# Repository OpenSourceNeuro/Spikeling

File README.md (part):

<div align="center">

# **Spikeling v3**

### **An open-source hardware + software platform for neuroscience teaching and outreach:**  

A hands-on “artificial spiking neuron” running the **Izhikevich model** on an **ESP32**, with a desktop **GUI** for visualization, interaction, and data export.

<p>

</p>

<p align="right">
  developed by M.J.Y. Zimmermann<br>
  maintained by P. Rignanese & A. Koumoundourou<br>
  based on an original idea by T. Baden
</p>

</div>

This project is licensed under the [GNU General Public License v3.0](https://www.gnu.org/licenses/gpl-3.0.en.html)
<br>
The hardware is licensed under the [ CERN-OHL-S-2.0](https://gitlab.com/ohwr/project/cernohl/-/wikis/uploads/b88fd806c337866bff655f2506f23d37/cern_ohl_s_v2_user_guide.txt)

## Contents

- [What is Spikeling?](#what-is-spikeling)
- [Spikeling in academia & outreach](#spikeling-in-academia--outreach)
- [A brief summary of Spikeling functions](#a-brief-summary-of-spikeling-functions)
  - [Neurophysiology](#neurophysiology)
  - [Data analysis](#data-analysis)
  - [Neuron generator](#neuron-generator)
  - [Stimulus generator](#stimulus-generator)
  - [Multi-recording & networking](#multi-recording--networking-multi-unit-experiments)
  - [Fluorescence imaging simulation](#fluorescence-imaging-simulation)
  - [Exercises](#exercises)
- [Documentation](#documentation)
- [Contributing](#contributing)
- [License](#license)

---

<br>

<div align="center">

## What is Spikeling?

<br>

<p style='text-align: justify;'>
  Spikeling is an open-source neuroscience education platform designed to make core neurophysiology concepts teachable through hands-on experimentation, even in settings where traditional wet-lab electrophysiology is impractical.
</p>

<p style='text-align: justify;'>
  In many degree programs, students learn about action potentials and synaptic signalling largely through lectures or static datasets because living preparations, microscopes, amplifiers, and specialist supervision do not scale well to large cohorts. Spikeling addresses this gap with a low-cost “in silico neuron” implemented in hardware.
</p>

<p style='text-align: justify;'>
  The device runs the computationally efficient and versatile <strong>Izhikevich spiking neuron model</strong> in real time on an ESP32-based microcontroller, providing electrophysiology-style interaction: controlled stimulation, measurable membrane-voltage dynamics, spike output, and parameter manipulation to explore firing regimes, adaptation, and input integration.
</p>

<p style='text-align: justify;'>
  A dedicated <strong>cross-platform desktop GUI</strong> supports real-time plotting, experiment control, and recording/export to standard formats—enabling teaching modules that extend beyond neurophysiology into protocol design, data collection, analysis pipelines, and model-based reasoning.
</p>

</div>

<br>

<div align="center">

<h6 align="center">Two spikeling units (red and green), that are synchronously stimulated (white cables), synapse with a third unit (blue).</h6>

</div>

---

<br>

<div align="center">

## Spikeling in academia & outreach

<br>

<p style='text-align: justify;'>
  The spikeling project emerged from local needs to teach neuroscience class modules for direct interaction with <strong>neuron physiology, data analysis, fluorescence imaging, protocol design, etc.</strong>
</p>

<p style='text-align: justify;'>
  The aim was to provide <strong>hands-on experience</strong> on how neurons encode information and how diverse variables modulates their activities, while engaging students with <strong>crucial aspects of data collection, experimental limitations, methodology and statistical analysis.</strong>
</p>

<p style='text-align: justify;'>
  Spikeling is currently used in <strong>university teaching, computational neuroscience training, and outreach events</strong>. It is intentionally <strong>open (hardware + firmware + software)</strong> so educators can customize activities for their courses and contribute back to a shared pool of teaching material.
</p>

<table>
  <tr>
    <td width="33%">
      <br>
      <sub><b>Outreach demonstration of neuron activities to primary school student in Ghana (2025)</b></sub>
    </td>
    <td width="33%">
      <br>
      <sub><b>Hands-on electrophysiology-style experiments in Zambia (2025)</b></sub>
    </td>
    <td width="33%">
      <br>
      <sub><b>Small-group protocol design & parameter exploration in Rwanda (2024)</b></sub>
    </td>
  </tr>

</table>

</div>

***

<br>

<div align="center">

## A brief summary of Spikeling functions

<br>

<h3 align="left"> Neurophysiology:</h3></p>

<p style='text-align: justify;'>
  Spikeling implements the <strong>Izhikevich model</strong>, which “reproduces spiking and bursting behaviour of known type of cortical neurons. The model combines the <strong>biologically plausibility of Hodgkin-Huxley-type dynamics</strong> and the <strong>computational efficiency of integrate-and-fire neurons</strong>” <a href="https://ieeexplore.ieee.org/document/1257420"> E. M. Izhikevich, "Simple model of spiking neurons, 2003"</a>.
  This makes it well-suited for teaching as learners can move quickly between <strong>hypothesis → stimulation → observation → interpretation</strong>.
</p>

<p style='text-align: justify;'>
  Neurophysiology concepts are taught through electrophysiology-style interaction: students apply controlled inputs and directly observe membrane-voltage dynamics,
  thresholding, spike generation, and adaptation. This supports practical teaching objectives such as protocol design, parameter sensitivity, and reproducible experimentation.
</p>

<ul align="left">
  <li>
    <b>Patch-clamp style stimulation (current injection):</b>
    A simulated patch-clamp interface allows students to inject controlled current steps and waveforms.
    Learners can vary <b>amplitude</b>, <b>duration</b>, and <b>timing</b> to explore excitability, threshold, refractory effects, and spike-frequency adaptation.
  </li>

  <li>
    <b>Photo-sensitive input (photodiode / “photoreceptor”):</b>
    Spikeling includes a photodiode input that mimics sensory-driven current input.
    Students can test simple stimuli (e.g., flashlight pulses) and progress to controlled protocols using an external LED driven via the stimulus port
    (frequency/intensity). Advanced discussions can include response dynamics such as effective decay/recovery behaviour under repeated stimulation.
  </li>

  <li>
    <b>Synapses and networks (dendrites + axon):</b>
    Each unit provides <b>two dendritic inputs</b> with gain and polarity control (supporting excitatory and inhibitory effects) and <b>one axonal spike output</b>.
    This enables multi-unit experiments on coincidence detection, inhibition-driven gating, synchrony, and simple network motifs.
    Auxiliary units can be stimulated synchronously to keep network experiments controlled and reproducible.
  </li>
</ul>

<p style='text-align: justify;'>
  Together, these features let students reproduce classic teaching experiments:
  step-current response curves, threshold measurements, adaptation quantification, sensory-driven spiking, and basic synaptic/network computations—using the same device and workflow.
</p>

<br>

<h6 align="center">Left: Drawing on the acrylic cover of the Spikeling version 2.2, representing the controls knobs along with the input/ouput jacks.

Right: Spikeling GUI displaying the unit membrane voltage (red trace) while being light-stimulated by a controlled LED (blue trace) which generates input current (green trace).
</h6>

</div>

***

<div align="center">

<h3 align="left"> Data analysis</h3></p>

<p style='text-align: justify;'>
  Spikeling is designed to extend practical teaching beyond “watching spikes” into the full experimental workflow:
  <strong>recording</strong>, <strong>quality control</strong>, <strong>basic quantification</strong>, and <strong>export for reproducible analysis</strong>.
  This is particularly valuable in neuroscience curricula where students may have limited exposure to programming and data pipelines, yet are expected to interpret real experimental data.
</p>

<p style='text-align: justify;'>
Any data generated by Spikeling can be <strong>saved and exported</strong> for downstream analysis. The GUI also provides a lightweight,
<strong>built-in analysis</strong> layer that helps students validate recordings and immediately compute core measures such as spike detection and trial-averaged responses.
This supports in-class demonstrations, rapid iteration during labs, and structured home assignments.
</p>

<p style='text-align: justify;'>
  For advanced data analysis and basic statistics, <strong>python notebooks</strong> are provided to serve as template for the teaching staff. We are engage with the Spikeling community where users could share courses, exercises and data analysis scripts to be widely used in neuroscience and coding courses.
</p>

<ul align="left">
  <li>
    <b>Recording & export:</b>
    save time series (e.g., Vm, stimulus, derived currents, triggers) and export to standard formats (e.g., <b>CSV</b>) compatible with Python, MATLAB, R, Excel, etc.
  </li>
  <li>
    <b>Basic QC and annotation:</b>
    quickly verify signal integrity, confirm stimulus timing, and identify artefacts before committing to a full analysis workflow.
  </li>
  <li>
    <b>Spike detection and raster plots:</b>
    detect spikes from membrane-voltage traces and visualize them as rasters to introduce spike trains, variability, and stimulus-locked responses.
  </li>
  <li>
    <b>Trial alignment, looping, and averaging:</b>
    repeat identical stimulus protocols, align trials, and compute averaged traces and spike-rate summaries—making it easy to teach concepts like reliability,
    response variability, and signal-to-noise.
  </li>
  <li>
    <b>Bridge to coding modules:</b>
    provide exported datasets and template <b>Python notebooks</b> so teaching staff can scaffold progressively from GUI-based inspection to student-written analysis code.
  </li>
</ul>

<p style='text-align: justify;'>
  In short, Spikeling supports a gradual learning curve: students can begin with GUI-based inspection and built-in metrics,
  then transition to reproducible, script-based analysis using the exact same datasets—mirroring modern research practice.
</p>
<br>

<h6 align="center">Left: Displayed data from the previous experiment (light stimulation) spikes are detected and ploted along the Vm trace (red). Right: Traces looped and averaged showing the spike rate (white), the raster plot (red dots), the averaged Vm recording (red) and the averaged input current (green)</h6>

</div>

***

<div align="center">

<h3 align="left"> Neuron generator</h3></p>

<p style='text-align: justify;'>
  The <strong>Neuron Generator</strong> is an interactive space for exploring the Izhikevich model beyond “playing with a few knobs”.
  It is designed to help students connect <strong>model parameters</strong> to <strong>observable firing behaviours</strong> (e.g., tonic spiking, bursting, adaptation, rebound, irregular firing),
  and to build intuition for how different neurons can emerge from the same compact set of equations.
</p>

<p style='text-align: justify;'>
  In practice, the Neuron Generator lets learners rapidly prototype neuron “types” by adjusting Izhikevich parameters and immediately observing
  how the neuron responds to standardized stimuli. This encourages a scientific workflow: formulate a hypothesis (e.g., “increasing adaptation should reduce firing rate over time”),
  test it with controlled stimulation, then iterate.
</p>

<ul align="left">
  <li><b>Explore firing regimes:</b> interactively vary Izhikevich parameters and observe changes in excitability, thresholding, bursting, and adaptation.</li>
  <li><b>Compare neurons under identical protocols:</b> run the same stimulus recipe on multiple parameter sets to build mechanistic intuition.</li>
  <li><b>Create & share presets:</b> save custom neuron parameter sets for labs, assignments, or reproducible classroom demonstrations.</li>
  <li><b>Bridge theory and experiment:</b> connect equations/parameters to patch-clamp-style readouts (Vm traces, spike trains, firing-rate changes).</li>
</ul>

<br>

<h6 align="center">GUI displaying the “Neuron Generator” page where users can appreciate the model underlying Spikeling activity and from which they can generate unique neuron to further run on Spikeling.</h6>

</div>

***

<div align="center">

<h3 align="left">Stimulus generator:</h3>

<p style='text-align: justify;'>
  Spikeling includes a dedicated <strong>Stimulus Generator</strong> to teach one of the most important (and often under-taught) parts of experimental neuroscience:
  <strong>protocol design</strong>. While Spikeling board only has a simple repeated square-wave stimulus (useful for classic current-step experiments and LED/light stimulation),
  the Stimulus Generator encourages students to move beyond “turning knobs” and instead design inputs that directly test experimental hypotheses.
</p>

<p style='text-align: justify;'>
  Users can create and iterate custom stimuli—such as <strong>step families</strong>, <strong>sinusoids</strong>, <strong>chirps</strong>, <strong>pulse trains</strong>, and <strong>binary/noise-like</strong> sequences—
  then apply them to current injection or light stimulation. A built-in <strong>stimulus preview</strong> allows learners to verify waveform timing, amplitude, and repetition structure
  <em>before</em> running an experiment, reinforcing good practice around sanity checks and reproducibility.
</p>

<ul align="left">
  <li><b>From standard to custom protocols:</b> start with square pulses and progress to structured waveforms used in electrophysiology and systems neuroscience.</li>
  <li><b>Preview before running:</b> confirm duration, inter-stimulus intervals, amplitude scaling, and repetition count to avoid protocol errors.</li>
  <li><b>Reproducible experimentation:</b> define explicit parameters to enable trial averaging and fair comparisons across neuron modes or conditions.</li>
  <li><b>Hypothesis-driven design:</b> link stimulus structure to questions like threshold, adaptation time constants, resonance, and response reliability under noise.</li>
</ul>

<br>

  <h6 align="center">
    Stimulus Generator examples (with preview). Left: classic electrophysiology-style step family (10 steps, 10 a.u. increment, 25 ms per step, 5 ms rest at 0 a.u.).
    Right: sine-wave stimulus (50 a.u. amplitude, 20 Hz, 250 ms duration, 100 ms rest at 0 a.u.).
  </h6>

</div>

***

<div align="center">

<h3 align="left">Multi-recording & networking (multi-unit experiments):</h3>

<p style='text-align: justify;'>
  A key strength of Spikeling is that it can be scaled from a single “neuron” demo to <strong>small, interpretable networks</strong>.
  Each unit provides an <strong>axonal spike output</strong> and two <strong>dendritic (synaptic) inputs</strong>, enabling multiple Spikelings to be physically connected
  and studied as a functional circuit. This makes it possible to teach network-level computation using the same workflow as single-cell experiments:
  controlled stimulation, direct observation, and quantitative comparison.
</p>

<p style='text-align: justify;'>
  Importantly, each synaptic input can be configured as <strong>excitatory or inhibitory</strong> (via the synaptic gain control), allowing learners to explore
  how the <strong>sign</strong> and <strong>strength</strong> of coupling shapes membrane dynamics and spiking output. The GUI supports <strong>multi-recording</strong> by plotting and saving,
  in the same session, the activity of the main unit alongside the incoming synaptic streams (and, when available, the associated presynaptic signals),
  which is essential for teaching causality, timing, and interaction effects.
</p>

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
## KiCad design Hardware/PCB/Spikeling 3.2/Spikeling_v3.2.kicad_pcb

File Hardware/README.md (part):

<div align="center">

# **Hardware design, assembly, and revision notes**

<p>

</p>

</div>

This folder contains the hardware side of **Spikeling**: board revisions, build notes, connector conventions, and practical guidance for bringing a unit from PCB to a working neuroscience teaching device.

Spikeling is an open hardware + software platform for hands-on neuroscience teaching and outreach. It exposes a spiking neuron model through real controls, real I/O, and real-time visualisation, allowing students to run electrophysiology-style experiments without a full wet-lab rig.

**Quick links**
- [Main repository](../)
- [Firmware folder](../Firmware)
- [Software folder](../Software)
- [Documentation folder](../Documentation)
- [Hardware documentation](https://opensourceneuro.github.io/Spikeling/hardware/)
- [Quickstart: hardware setup](https://opensourceneuro.github.io/Spikeling/quickstart/hardware-setup/)
- [Reference: pinout and connectors](https://opensourceneuro.github.io/Spikeling/reference/pinout-and-connectors/)
- [Reference: specs](https://opensourceneuro.github.io/Spikeling/reference/specs/)

<p align="right">
  developed by M.J.Y. Zimmermann<br>
  maintained by P. Rignanese & A. Koumoundourou<br>
  based on an original idea by T. Baden
</p>

---

## **1. What this folder is for**

Use the `Hardware` folder as the entry point for:

- PCB design files and revision history
- manufacturing outputs and sourcing material
- assembly notes and bring-up checks
- connector / wiring conventions
- calibration and troubleshooting notes
- hardware differences between Spikeling generations

This README is meant to help contributors, builders, and teaching staff quickly understand which board they have, how it differs from other revisions, and where to find the next level of detail.

---

## **2. Hardware families**

Spikeling currently exists in two official board families.

### **Spikeling v2.x**
- **Microcontroller:** ESP32 WROOM-32
- **USB connector:** mini-USB
- **USB behaviour:** USB-to-UART bridge (**CP210x**)
- **Driver requirement:** often required, especially on Windows
- **Neuron mode selection:** on-board **Mode** button
- **Preset neuron modes:** 12

### **Spikeling v3.x**
- **Microcontroller:** ESP32-S3 WROOM-1
- **USB connector:** USB-C
- **USB behaviour:** native USB (**USB CDC serial**)
- **Driver requirement:** typically no separate USB-UART driver required
- **Neuron mode selection:** from the **GUI**
- **Preset neuron modes:** 20
- **Additional hardware compared to v2.x:** external DAC IC
- **Additional convenience features:** LiPo power-control hardware and a dedicated control to disable the Vm LED

> In practice, both families support the same teaching workflow: stimulate the model neuron, observe Vm and spikes, connect units together, and record/export data. The main differences affect USB connection, firmware target, mode selection, and a few hardware conveniences.

---

## **3. Version 2 vs version 3 — practical differences**

### **Connection and setup**
- **v2.x** uses a CP210x USB-to-UART bridge, so serial detection depends on that driver being installed.
- **v3.x** uses the ESP32-S3 native USB interface and usually enumerates directly as a USB serial device.

### **User interaction**
- **v2.x** changes neuron behaviour using an on-board **Mode** button.
- **v3.x** moves neuron mode selection into the GUI, which makes classroom switching and software-driven workflows more convenient.

### **Analogue output hardware**
- **v3.x** adds an external DAC compared with **v2.x**, improving the hardware architecture for the newer board generation.

### **Power and convenience controls**
- **v3.x** adds hardware support for the LiPo extension and includes a control to disable the Vm LED.
- **v2.x** is the simpler earlier platform and is closer to the minimal USB-to-ESP32 teaching-board architecture.

### **How to identify them quickly**
- **mini-USB = v2.x**
- **USB-C = v3.x**

---

## **4. What Spikeling hardware does**

At the hardware level, Spikeling behaves like a compact teaching-oriented electrophysiology preparation:

- multiple input pathways contribute to the neuron’s total drive
- the board exposes a measurable membrane potential (**Vm**)
- threshold crossings generate discrete spike events
- the board streams signals to the desktop GUI for visualisation, stimulation, and recording

### **Main input pathways**
- current injection control
- on-board square-wave stimulus generator
- GUI-driven stimulus generator
- photodiode input for light stimulation
- Synapse 1 / Synapse 2 inputs from other Spikeling units

### **Main outputs**
- analogue **Vm**
- digital spike events
- stimulus output for external use
- real-time USB serial stream to the GUI

---

## **5. Controls and I/O philosophy**

Spikeling uses **3.5 mm stereo TRS jacks** to carry both analogue and digital signals with a shared ground.

### **TRS convention**
- **Tip (T)** = digital / TTL
- **Ring (R)** = analogue signal
- **Sleeve (S)** = ground

This makes the hardware compact and classroom-friendly: one cable can carry both a continuously varying signal and an event marker.

### **Typical signal roles**
- **Synaptic / axon output:** analogue = presynaptic Vm, digital = spike events
- **Stimulus output:** analogue = stimulus waveform, digital = PWM / timing signal
- **Synapse input 1 / 2:** receives a TRS feed from another unit
- **Current input:** receives an injected analogue waveform
- **Photodiode workflow:** an LED driven through the stimulus path can act as a controlled light stimulus

### **Common wiring patterns**
- **Axon output (unit A) → Synapse input (unit B)** for two-unit network experiments
- **Stimulus output → LED cable → photodiode** for controlled light stimulation
- **Stimulus output → current input** for waveform-based injected current experiments

> Ground continuity matters. Many noisy or unstable measurements are caused by missing or inconsistent ground reference on the TRS sleeve.

---

## **6. Core teaching-facing controls**

The exact silkscreen may vary slightly between revisions, but the core controls remain conceptually stable.

- **Current injection**: direct depolarising / hyperpolarising drive
- **Stimulus strength**: amplitude of the on-board square-wave drive
- **Stimulus frequency**: repetition rate of the on-board stimulus
- **Noise**: Gaussian noise added to the input drive
- **Photo gain (±)**: gain and polarity of the photodiode input
- **Synapse 1 gain (±)**: excitatory or inhibitory strength of synapse 1
- **Synapse 2 gain (±)**: excitatory or inhibitory strength of synapse 2
- **Reset**: return the board to a known state
- **Buzzer mute**: disable spike audio feedback

### **Revision-specific controls**
- **v2.x:** Mode button selects one of 12 preset Izhikevich parameter sets
- **v3.x:** neuron mode is selected in the GUI, and the board adds:
  - **Vm LED disable**
  - **LiPo power switch / power-control hardware**

---

## **7. Minimum hardware needed to use a board**

### **For either generation**
- one Spikeling unit
- one data-capable USB cable
- at least one **3.5 mm TRS stereo cable**
- a computer running the GUI
- optionally, an LED stimulus cable for photodiode experiments

### **Board-specific USB cables**
- **v2.x:** mini-USB data cable
- **v3.x:** USB-C data cable

### **Recommended extras**
- powered USB hub
- spare TRS patch cables
- TRS-to-breakout adapter(s)
- multimeter
- optional oscilloscope or logic analyser for debugging

---

## **8. Quick bring-up checklist**

Before troubleshooting firmware or GUI issues, confirm the physical layer first.

- I know whether the board is **v2.x** or **v3.x**
- I am using a **data-capable** USB cable
- The board appears as a serial device on the computer
- For **v2.x**, the **CP210x** driver is installed
- I have at least one known-good **TRS** cable
- I understand the **Tip / Ring / Sleeve** mapping
- No other application is already holding the serial port
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
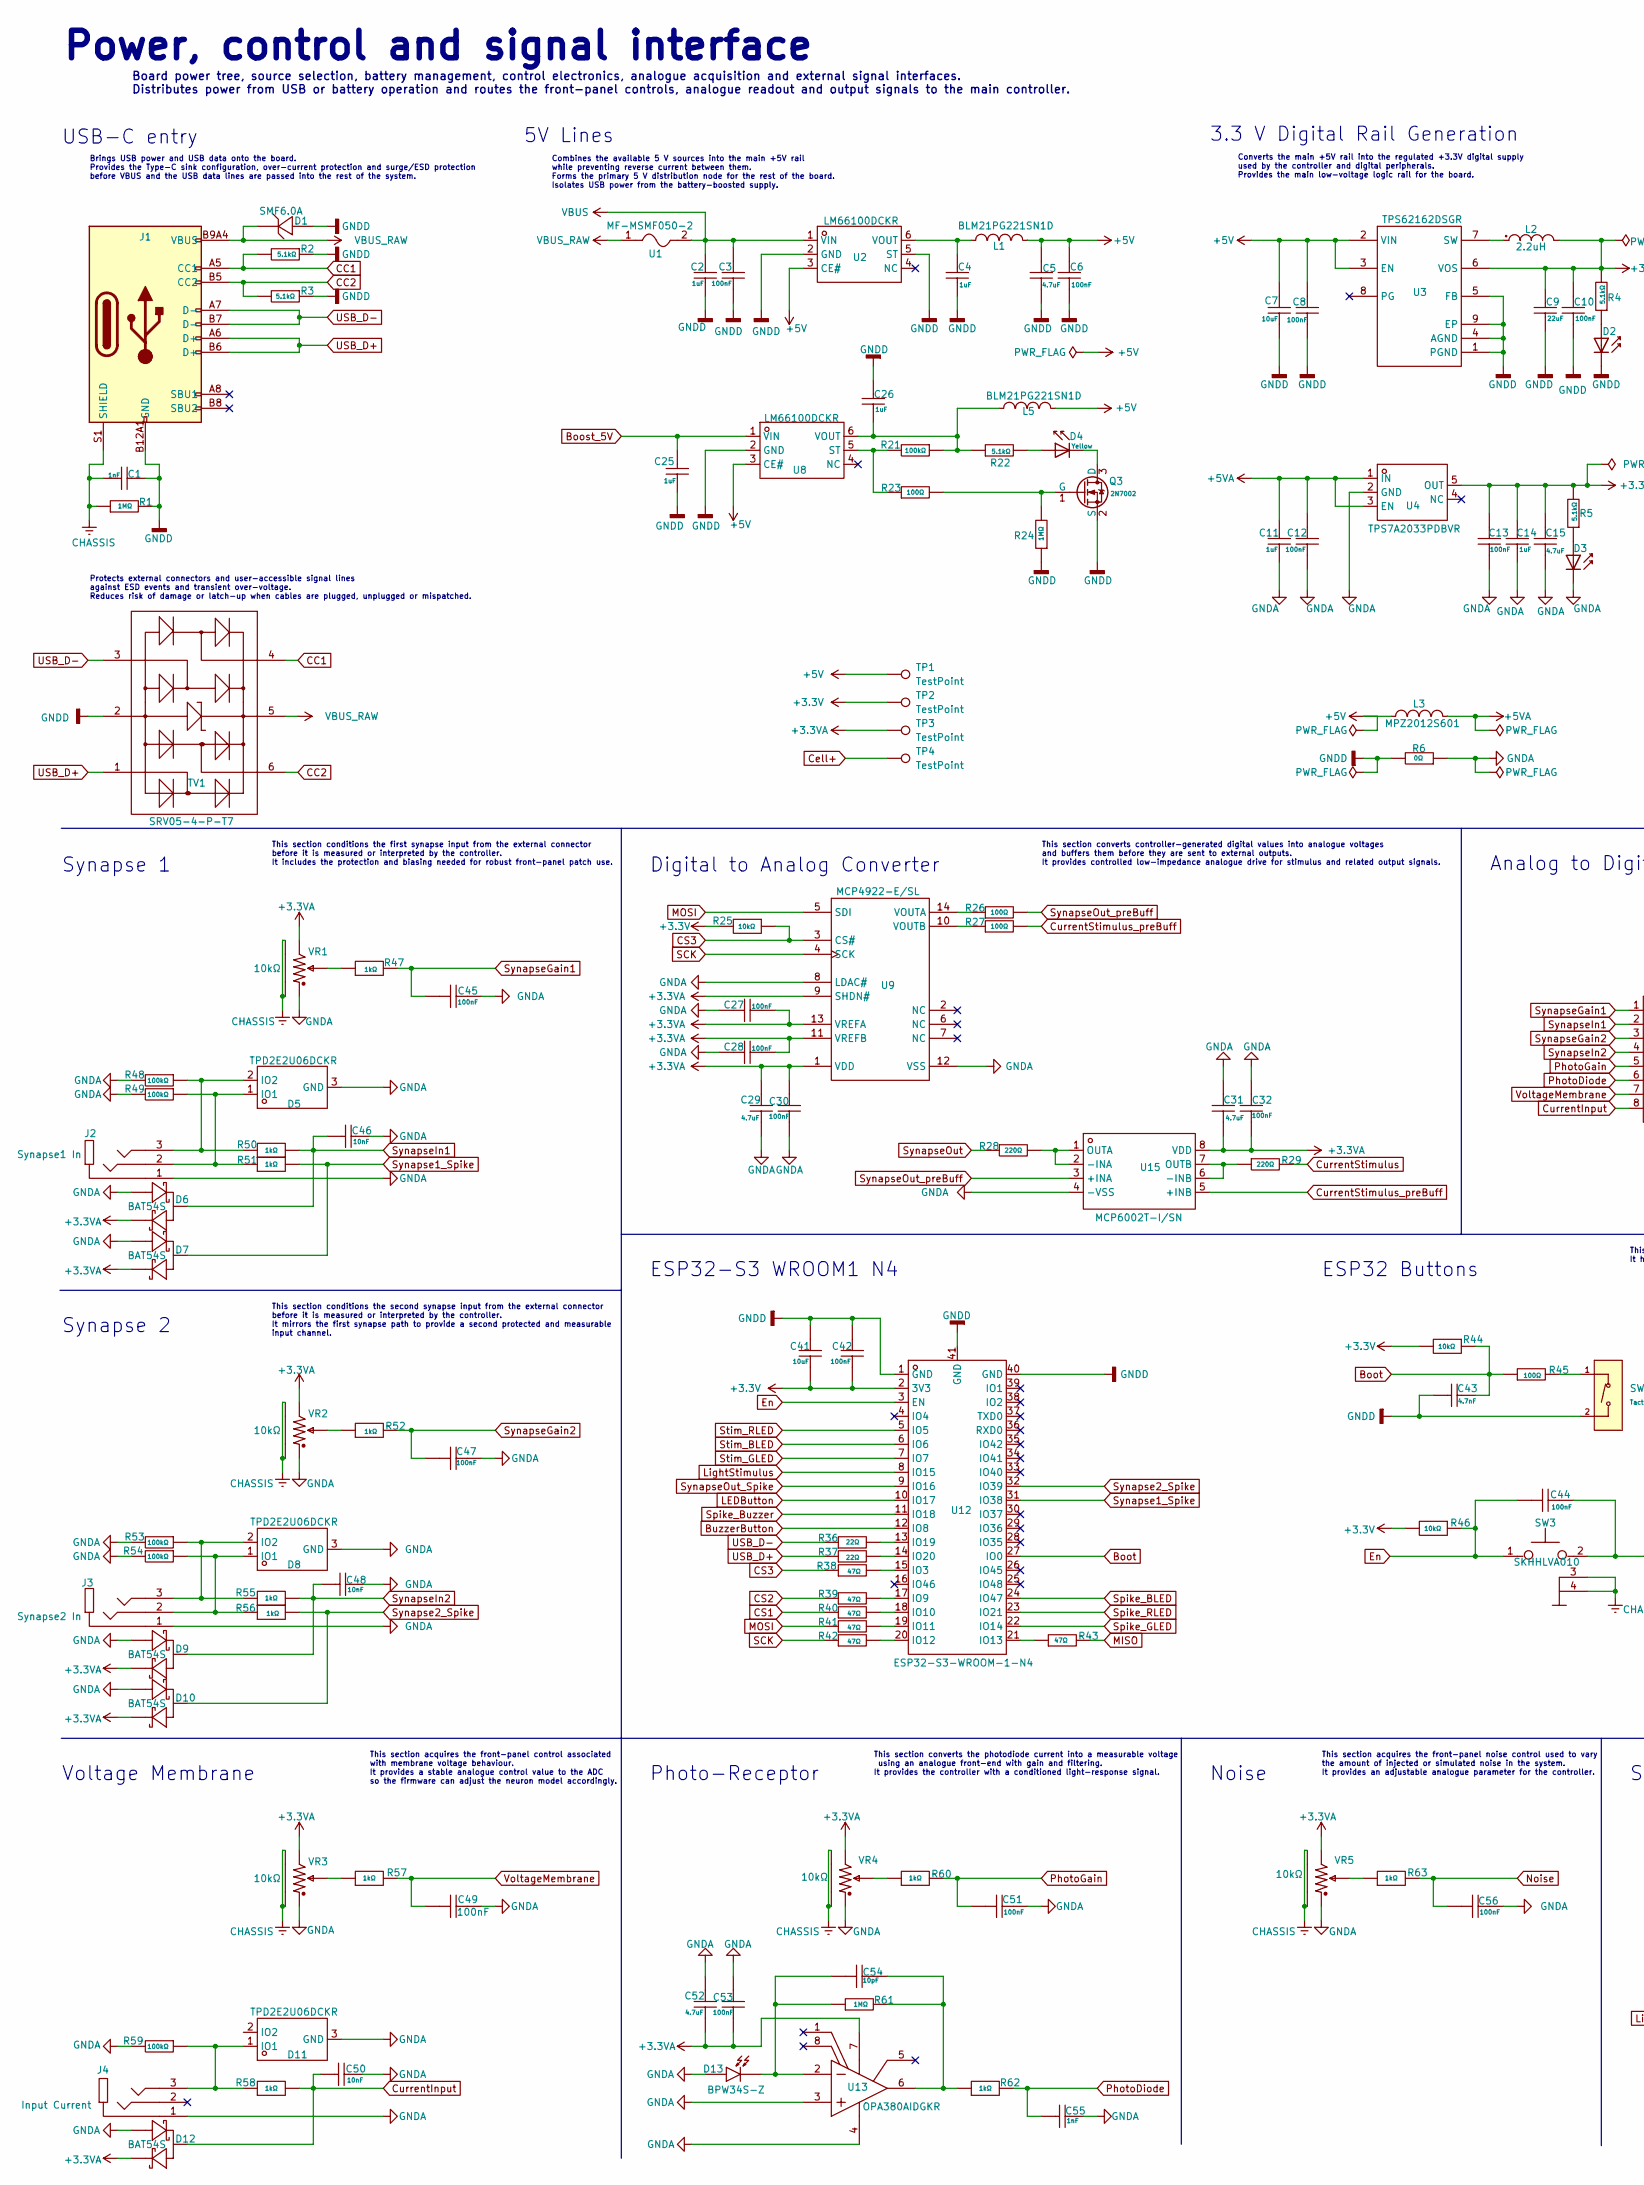
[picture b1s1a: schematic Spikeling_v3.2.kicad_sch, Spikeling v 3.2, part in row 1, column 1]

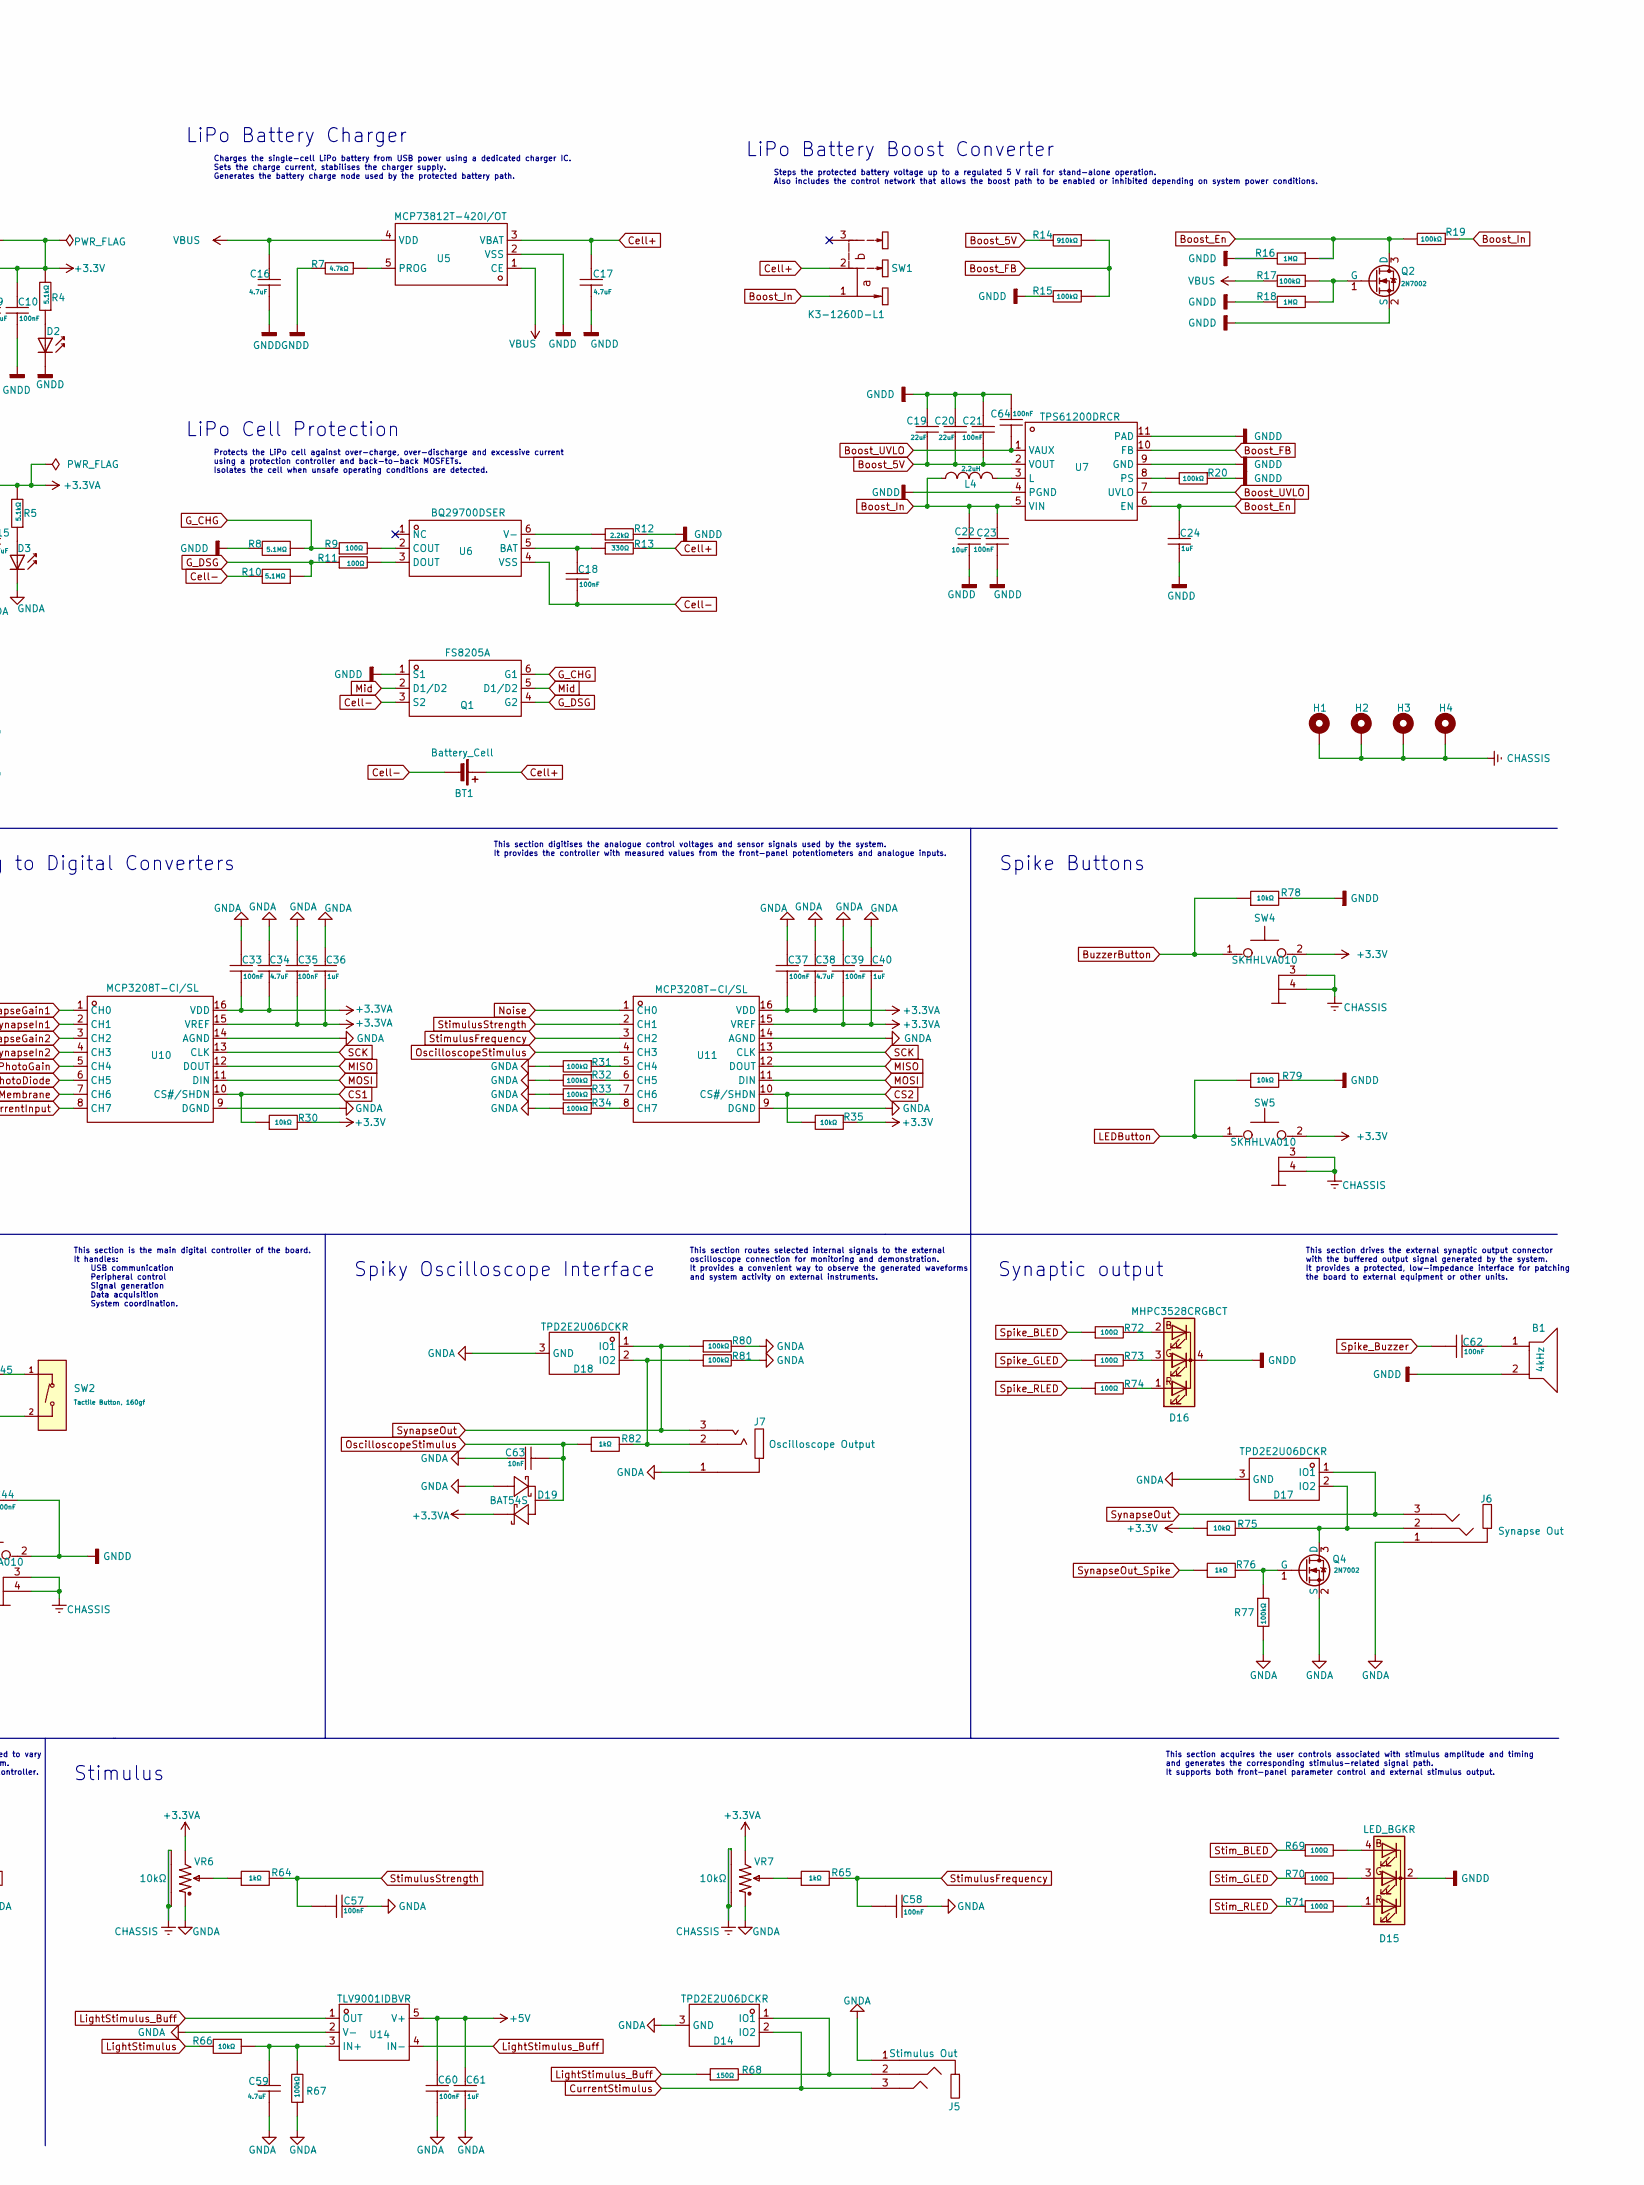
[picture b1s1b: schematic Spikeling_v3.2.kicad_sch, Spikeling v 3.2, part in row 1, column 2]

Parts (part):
B1: 4kHz; BUZ-TH_L12.0-W12.0; LCSC Part # C7421651
BT1: Battery_Cell; JST_XH_B2B-XH-A_1x02_P2.50mm_Vertical; LCSC Part # C265283
C1, C55: 1nF; C_0603; TOLERANCE ±10%; MANUFACTURER PART CC0603KRX7R9BB102; LCSC PART NAME 1nF ±10% 50V
C2, C4, C11, C14, C24, C25, C26, C36, C40, C61: 1uF; C_0805; TOLERANCE ±10%; VOLTAGE RATING 50V; MANUFACTURER PART CL21B105KBFNNNE; LCSC PART NAME 1uF ±10% 50V
C3, C6, C8, C10, C12, C13, C18, C21, C23, C27, C28, C30, C32, C33, C35, C37, C39, C42, C44, C45, C47, C49, C51, C53, C56, C57, C58, C60, C62, C64: 100nF; C_0603; TOLERANCE ±10%; VOLTAGE RATING 50V; MANUFACTURER PART CL10B104KB8NNNC; LCSC PART NAME 100nF ±10% 50V
C5, C15, C16, C17, C29, C31, C34, C38, C52, C59: 4.7uF; C_0805; TOLERANCE ±10%; VOLTAGE RATING 35V; MANUFACTURER PART CS2012X7R475K350NRE; LCSC PART NAME 4.7uF ±10% 35V
C7, C22: 10uF; C_1206; TOLERANCE ±10%; VOLTAGE RATING 25V; MANUFACTURER PART TCC1206X7R106K250HT; LCSC PART NAME 10uF ±10% 25V
C9, C19, C20: 22uF; C_1206; TOLERANCE ±10%; VOLTAGE RATING 25V; MANUFACTURER PART CL31A226KAHNNNE; LCSC PART NAME 22uF ±10% 25V
C41: 10uF; C_0805; TOLERANCE ±10%; VOLTAGE RATING 50V; MANUFACTURER PART CL21A106KBYQNNE; LCSC PART NAME 10uF ±10% 50V
C43: 4.7nF; C_0603; TOLERANCE ±10%; VOLTAGE RATING 50V; MANUFACTURER PART 0603B472K500NT; LCSC PART NAME 4.7nF ±10% 50V
C46, C48, C50, C63: 10nF; C_0603; TOLERANCE ±10%; VOLTAGE RATING 50V; MANUFACTURER PART CC0603KRX7R9BB103; LCSC PART NAME 10nF ±10% 50V
C54: 10pF; C_0603; TOLERANCE ±5%; VOLTAGE RATING 50V; MANUFACTURER PART 0603CG100J500NT; LCSC PART NAME 10pF ±5% 50V
D1: SMF6.0A; D_SOD-123FL; CLAMPING VOLTAGE 10.3V; VOLTAGE - BREAKDOWN 7.37V; MANUFACTURER PART SMF6.0A; LCSC PART NAME 单向TVS 6V截止 峰值浪涌电流：19.4A@10/1000us
D2, D3: Red; D_0603; Part KT-0603R; LCSC Part # C2286
D4: Yellow; D_0603; Forward Voltage (VF) 1.6V~2.6V; Part NCD0603Y2; LCSC Part # C89811
D5, D8, D11, D14, D17, D18: TPD2E2U06DCKR; SC-70-3_L2.0-W1.3-P0.65-LS2.1-BL; BREAKDOWN VOLTAGE 6.5V; MANUFACTURER PART TPD2E2U06DCKR; LCSC PART NAME TPD2E2U06DCKR
D6, D7, D9, D10, D12, D19: BAT54S; SOT-23-3_L2.9-W1.3-P1.90-LS2.4-BR; VOLTAGE - FORWARD(VF@IF) 800mV@100mA; VOLTAGE - DC REVERSE(VR) 30V; MANUFACTURER PART BAT54S; LCSC PART NAME 电压:30V 电流:200mA
D13: BPW34S-Z; SENSOR-TH_BPW34S-Z; MANUFACTURER PART BPW34S-Z; LCSC PART NAME 920nm 频谱范围420nm~1120nm 反向电压32V
D15: LED_BGKR; LED_Kingbright_APFA3010_3x1.5mm_Horizontal
D16: MHPC3528CRGBCT; LED-SMD_4P-L3.2-W2.8-BL; LCSC PART NAME RGB三色 正贴
H1, H2, H3, H4: MountingHole_Pad; MountingHole_3.2mm_M3_DIN965_Pad
J1: Connector, USB-TYPE-C-16P; TYPE-C-SMD_HX-TYPE-C-16PIN; LCSC Part # C2927039
J2: Synapse1 In; AUDIO-SMD_HX-PJ-320A-3P-DIP; CURRENT RATING 500mA; VOLTAGE RATING (MAX) 30V; MANUFACTURER PART HX PJ-320A-3P DIP; LCSC PART NAME 3.5mm耳机座
J3: Synapse2 In; AUDIO-SMD_HX-PJ-320A-3P-DIP; CURRENT RATING 500mA; VOLTAGE RATING (MAX) 30V; MANUFACTURER PART HX PJ-320A-3P DIP; LCSC PART NAME 3.5mm耳机座
J4: Input Current; AUDIO-SMD_HX-PJ-320A-3P-DIP; CURRENT RATING 500mA; VOLTAGE RATING (MAX) 30V; MANUFACTURER PART HX PJ-320A-3P DIP; LCSC PART NAME 3.5mm耳机座
J5: Stimulus Out; AUDIO-SMD_HX-PJ-320A-3P-DIP; CURRENT RATING 500mA; VOLTAGE RATING (MAX) 30V; MANUFACTURER PART HX PJ-320A-3P DIP; LCSC PART NAME 3.5mm耳机座
J6: Synapse Out; AUDIO-SMD_HX-PJ-320A-3P-DIP; CURRENT RATING 500mA; VOLTAGE RATING (MAX) 30V; MANUFACTURER PART HX PJ-320A-3P DIP; LCSC PART NAME 3.5mm耳机座
J7: Oscilloscope Output; AUDIO-SMD_PJ-320B; CURRENT RATING (MAX) 200mA; VOLTAGE RATING (MAX) 30V; MANUFACTURER PART PJ-320B贴片; LCSC PART NAME 3.5mm耳机座
L1, L5: BLM21PG221SN1D; L0805; TOLERANCE ±25%; CURRENT RATING 2A; MANUFACTURER PART BLM21PG221SN1D; LCSC PART NAME 单路 0805磁珠 阻抗220Ω@100MHz
L2: 2.2uH; IND-SMD_L3.0-W3.0_XFL3012; TOLERANCE ±20%; CURRENT RATING 1.9A; MANUFACTURER PART XFL3012-222MEC; LCSC PART NAME 2.2uH ±20% 1.6A
L3: MPZ2012S601; L_0805; TOLERANCE ±25%; CURRENT RATING 2A; MANUFACTURER PART MPZ2012S601AT000; LCSC PART NAME 单路 0805磁珠 阻抗600Ω@100MHz
L4: 2.2uH; IND-SMD_L4.4-W4.0_PHC0420; TOLERANCE ±20%; CURRENT RATING 4.5A; MANUFACTURER PART APH0420T2R2M; LCSC PART NAME 2.2uH ±20% 5A
Q1: FS8205A; SOT-23-6_L2.9-W1.6-P0.95-LS2.8-BR; MANUFACTURER PART FS8205A; LCSC PART NAME 2个N沟道 耐压:20V 电流:6A
Q2, Q3, Q4: 2N7002; Q_SOT-23; Part 2N7002; LCSC Part # C8545
R1, R16, R18, R24, R61: 1MΩ; R_0603; TOLERANCE ±1%; MANUFACTURER PART RC0603FR-071ML; LCSC PART NAME 厚膜电阻 1MΩ ±1% 100mW
R2, R3, R4, R5, R22: 5.1kΩ; R_0603; TOLERANCE ±1%; VOLTAGE-SUPPLY(MAX) 75V; MANUFACTURER PART 0603WAF5101T5E; LCSC PART NAME 5.1kΩ ±1% 100mW 厚膜电阻
R6: 0Ω; R_0603; TOLERANCE ±1%; VOLTAGE-SUPPLY(MAX) 75V; MANUFACTURER PART 0603WAF0000T5E; LCSC PART NAME 0Ω ±1% 100mW 厚膜电阻
R7: 4.7kΩ; R_0603; TOLERANCE ±1%; VOLTAGE-SUPPLY(MAX) 75V; MANUFACTURER PART 0603WAF4701T5E; LCSC PART NAME 4.7kΩ ±1% 100mW 厚膜电阻
R8, R10: 5.1MΩ; R_0603; TOLERANCE ±1%; VOLTAGE-SUPPLY(MAX) 75V; MANUFACTURER PART AC0603FR-075M1L; LCSC PART NAME 厚膜电阻 5.1MΩ ±1% 100mW
R9, R11, R23, R26, R27, R45, R69, R70, R71, R72, R73, R74: 100Ω; R_0603; TOLERANCE ±1%; MANUFACTURER PART RC0603FR-07100RL; LCSC PART NAME 厚膜电阻 100Ω ±1% 100mW
R12: 2.2kΩ; R_0603; TOLERANCE ±1%; MANUFACTURER PART 0603WAF2201T5E; LCSC PART NAME 2.2kΩ ±1% 100mW 厚膜电阻
R13: 330Ω; R_0603; TOLERANCE ±1%; MANUFACTURER PART 0603WAF3300T5E; LCSC PART NAME 330Ω ±1% 100mW 厚膜电阻
R14: 910kΩ; R_0603; TOLERANCE ±1%; MANUFACTURER PART 0603WAF9103T5E; LCSC PART NAME 910kΩ ±1% 100mW 厚膜电阻
R15, R17, R19, R20, R21, R31, R32, R33, R34, R48, R49, R53, R54, R59, R67, R77, R80, R81: 100kΩ; R_0603; TOLERANCE ±1%; MANUFACTURER PART RC0603FR-07100KL; LCSC PART NAME 厚膜电阻 100kΩ ±1% 100mW
R25, R30, R35, R44, R46, R66, R75, R78, R79: 10kΩ; R_0603; TOLERANCE ±1%; VOLTAGE-SUPPLY(MAX) 75V; MANUFACTURER PART FRC0603F1002TS; LCSC PART NAME 10kΩ ±1% 100mW 厚膜电阻
R28, R29: 220Ω; R_0603; TOLERANCE ±1%; VOLTAGE-SUPPLY(MAX) 75V; MANUFACTURER PART RC0603FR-07220RL; LCSC PART NAME 厚膜电阻 220Ω ±1% 100mW
R36, R37: 22Ω; R_0603; TOLERANCE ±1%; MANUFACTURER PART 0603WAF220JT5E; LCSC PART NAME 22Ω ±1% 100mW 厚膜电阻
R38, R39, R40, R41, R42, R43: 47Ω; R_0603; TOLERANCE ±1%; VOLTAGE-SUPPLY(MAX) 75V; MANUFACTURER PART 0603WAF470JT5E; LCSC PART NAME 47Ω ±1% 100mW 厚膜电阻
R47, R50, R51, R52, R55, R56, R57, R58, R60, R62, R63, R64, R65, R76, R82: 1kΩ; R_0603; TOLERANCE ±1%; VOLTAGE-SUPPLY(MAX) 75V; MANUFACTURER PART FRC0603F1001TS; LCSC PART NAME 1kΩ ±1% 100mW 厚膜电阻
R68: 150Ω; R_0603; TOLERANCE ±1%; MANUFACTURER PART 0603WAF1500T5E; LCSC PART NAME 150Ω ±1% 100mW 厚膜电阻
SW1: K3-1260D-L1; SW-TH_K3-1260D-L1; CURRENT RATING 300mA; VOLTAGE RATING 6V; MANUFACTURER PART K3-1260D-L1; LCSC PART NAME 卧插双档 滑动开关
SW2: Tactile Button, 160gf; SW_TS-1088-AR02016; Part TS-1088-AR02016; LCSC Part # C720477
SW3, SW4, SW5: SKHHLVA010; KEY-TH_4P-L7.5-W6.8-P4.50-LS7.2; VOLTAGE RATING (DC) 12V; MANUFACTURER PART SKHHLVA010; LCSC PART NAME 6*6*5.85mm 卧插 轻触开关
TP1, TP2, TP3, TP4: TestPoint; TestPoint_Pad_D2.0mm
TV1: SRV05-4-P-T7; SOT-23-6_L2.9-W1.6-P0.95-LS2.8-BR; CLAMPING VOLTAGE 12V; VOLTAGE - BREAKDOWN 6V; MANUFACTURER PART SRV05-4-P-T7; LCSC Part ESD 5V截止 峰值浪涌电流：1A@8/20us
U1: MF-MSMF050-2; F1812; VOLTAGE - MAX 15V; MANUFACTURER PART MF-MSMF050-2; LCSC PART NAME 15V 500mA 1812自恢复
U2, U8: LM66100DCKR; SC-70-6_L2.0-W1.3-P0.65-LS2.1-BL; MANUFACTURER PART LM66100DCKR; LCSC PART NAME 5.5V 1.5A 低静态电流理想二极管
U3: TPS62162DSGR; WSON-8_L2.0-W2.0-P0.50-TL-EP; VOLTAGE - SUPPLY 3V~17V; OUTPUT VOLTAGE 3.3V; MANUFACTURER PART TPS62162DSGR; LCSC PART NAME 降压型 1A 3V~17V
U4: TPS7A2033PDBVR; SOT-23-5_L2.9-W1.6-P0.95-LS2.8-BR; OUTPUT VOLTAGE 3.3V; DROPOUT VOLTAGE 140mV@(300mA); MANUFACTURER PART TPS7A2033PDBVR; LCSC PART NAME 具有高 PSRR 的 300mA、超低噪声、低 IQ、低压降 (LDO) 线性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
U5: MCP73812T-420I/OT; SOT-23-5_L3.0-W1.7-P0.95-LS2.8-BR; VOLTAGE - SUPPLY 3.75V~6V; MANUFACTURER PART MCP73812T-420I/OT; LCSC PART NAME 单节锂离子/聚合物电池充电管理控制器
U6: BQ29700DSER; WSON-6_L1.5-W1.5-P0.50-TL; VOLTAGE - SUPPLY -300mV~8V; MANUFACTURER PART BQ29700DSER; LCSC PART NAME BQ29700DSER
U7: TPS61200DRCR; VSON-10_L3.0-W3.0-P0.50-TL-EP_TPS62410DRCR; VOLTAGE - SUPPLY 300mV~5.5V; OUTPUT VOLTAGE 1.8V~5.5V; MANUFACTURER PART TPS61200DRCR; LCSC PART NAME 低输入电压同步升压转换器
U9: MCP4922-E/SL; SOIC-14_L8.7-W3.9-P1.27-LS6.0-BL; VOLTAGE - SUPPLY 2.7V~5.5V; VOLTAGE REFERENCE External; MANUFACTURER PART MCP4922-E/SL; LCSC PART NAME MCP4922-E/SL
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
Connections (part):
+3.3V: C9.2, C10.2, C41.1, C42.1, L2.2, R4.2, R25.2, R30.2, R35.1, R44.2, R46.2, R75.1, SW4.2, SW5.2, TP2.1 (1_1), U3.6 (VOS), U12.2 (3V3)
+3.3VA: C13.2, C14.2, C15.2, C27.1, C28.1, C29.2, C30.2, C31.1, C32.2, C33.1, C34.1, C35.1, C36.1, C37.1, C38.1, C39.1, C40.1, C52.1, C53.1, D6.2 (K), D7.2 (K), D9.2 (K), D10.2 (K), D12.2 (K), D19.2 (K), R5.2, TP3.1 (1_1), U4.5 (OUT), U9.1 (VDD), U9.9 (SHDN#), U9.11 (VREFB), U9.13 (VREFA), U10.15 (VREF), U10.16 (VDD), U11.15 (VREF), U11.16 (VDD), U13.7 (V+), U15.8 (VDD), VR1.3, VR2.3, VR3.3, VR4.3, VR5.3, VR6.3, VR7.3
+5V: C5.2, C6.2, C7.2, C8.2, C60.2, C61.2, L1.2, L3.1, L5.2, TP1.1 (1_1), U2.3 (CE#), U3.2 (VIN), U3.3 (EN), U8.3 (CE#), U14.5 (V+)
+5VA: C11.2, C12.2, L3.2, U4.1 (IN), U4.3 (EN)
Boost_5V: C19.1, C20.1, C21.1, C25.2, R14.2, U7.2 (VOUT), U8.1 (VIN)
Boost_En: C24.1, Q2.3 (D), R16.1, R19.2, U7.6 (EN)
Boost_FB: R14.1, R15.1, U7.10 (FB)
Boost_In: C22.2, C23.2, L4.1, R19.1, SW1.1, U7.5 (VIN)
Boost_UVLO: C64.1, U7.1 (VAUX), U7.7 (UVLO)
Boot: C43.1, R44.1, R45.1, U12.27 (IO0)
BuzzerButton: R78.1, SW4.1, U12.12 (IO8)
CC1: J1.A5 (CC1), R2.2, TV1.4
CC2: J1.B5 (CC2), R3.2, TV1.6
CHASSIS: C1.1, H1.1 (1_1), H2.1 (1_1), H3.1 (1_1), H4.1 (1_1), J1.S1 (SHIELD), R1.1, SW3.3, SW3.4, SW4.3, SW4.4, SW5.3, SW5.4, VR1.4, VR1.5, VR2.4, VR2.5, VR3.4, VR3.5, VR4.4, VR4.5, VR5.4, VR5.5, VR6.4, VR6.5, VR7.4, VR7.5
CS1: R30.1, R40.1, U10.10 (CS#/SHDN)
CS2: R35.2, R39.1, U11.10 (CS#/SHDN)
CS3: R25.1, R38.1, U9.3 (CS#)
Cell+: BT1.1 (+), C17.2, R13.2, SW1.2, TP4.1 (1_1), U5.3 (VBAT)
Cell-: BT1.2 (-), C18.1, Q1.3 (S2), R10.2, U6.4 (VSS)
CurrentInput: C50.2, D12.3, R58.2, U10.8 (CH7)
CurrentStimulus: D14.2 (IO2), J5.3 (T), R29.2
CurrentStimulus_preBuff: R27.2, U15.5 (+INB)
En: C44.1, R46.1, SW3.1, U12.3 (EN)
GNDA: C11.1, C12.1, C13.1, C14.1, C15.1, C27.2, C28.2, C29.1, C30.1, C31.2, C32.1, C33.2, C34.2, C35.2, C36.2, C37.2, C38.2, C39.2, C40.2, C45.1, C46.2, C47.1, C48.2, C49.1, C50.1, C51.1, C52.2, C53.2, C55.1, C56.1, C57.1, C58.1, C59.1, C60.1, C61.1, C63.1, D3.1, D5.3 (GND), D6.1 (A), D7.1 (A), D8.3 (GND), D9.1 (A), D10.1 (A), D11.3 (GND), D12.1 (A), D13.1 (A), D14.3 (GND), D17.3 (GND), D18.3 (GND), D19.1 (A), J2.1 (S), J3.1 (S), J4.1 (S), J5.1 (S), J6.1 (S), J7.1, Q4.2 (S), R6.1, R31.2, R32.2, R33.2, R34.2, R48.2, R49.2, R53.2, R54.2, R59.2, R67.1, R77.2, R80.2, R81.2, U4.2 (GND), U9.8 (LDAC#), U9.12 (VSS), U10.9 (DGND), U10.14 (AGND), U11.9 (DGND), U11.14 (AGND), U13.3 (IN+), U13.4 (V-), U14.2 (V-), U15.4 (-VSS)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
GNDD: B1.2, C1.2, C2.1, C3.1, C4.1, C5.1, C6.1, C7.1, C8.1, C9.1, C10.1, C16.1, C17.1, C19.2, C20.2, C21.2, C22.1, C23.1, C24.2, C25.1, C26.2, C41.2, C42.2, C43.2, C44.2, C64.2, D1.2 (A), D2.1, D15.2 (K), D16.4 (K), J1.A12B1 (GND), J1.B12A1 (GND), Q1.1 (S1), Q2.2 (S), Q3.2 (S), R1.2, R2.1, R3.1, R6.2, R7.2, R8.2, R12.2, R15.2, R16.2, R18.2, R20.1, R24.1, R78.2, R79.2, SW2.2 (B), SW3.2, TV1.2, U2.2 (GND), U2.5 (ST), U3.1 (PGND), U3.4 (AGND), U3.5 (FB), U3.9 (EP), U5.2 (VSS), U7.4 (PGND), U7.9 (GND), U7.11 (PAD), U8.2 (GND), U12.1 (GND), U12.40 (GND), U12.41 (GND)
G_CHG: Q1.6 (G1), R8.1, R9.1
G_DSG: Q1.4 (G2), R10.1, R11.1
LEDButton: R79.1, SW5.1, U12.10 (IO17)
LightStimulus: R66.2, U12.8 (IO15)
LightStimulus_Buff: R68.1, U14.1 (OUT), U14.4 (IN-)
MISO: R43.2, U10.12 (DOUT), U11.12 (DOUT)
MOSI: R41.1, U9.5 (SDI), U10.11 (DIN), U11.11 (DIN)
Mid: Q1.2 (D1/D2), Q1.5 (D1/D2)
unnamed: B1.1, C62.2
unnamed: D2.2, R4.1
unnamed: D3.2, R5.1
unnamed: D4.2, R22.2
unnamed: D5.1 (IO1), J2.2 (R), R49.1, R51.1
unnamed: D5.2 (IO2), J2.3 (T), R48.1, R50.1
unnamed: D8.1 (IO1), J3.2 (R), R54.1, R56.1
unnamed: D8.2 (IO2), J3.3 (T), R53.1, R55.1
unnamed: D11.1 (IO1), J4.3 (T), R58.1, R59.1
unnamed: C54.1, D13.2 (C), R61.1, U13.2 (IN-)
unnamed: D14.1 (IO1), J5.2 (R), R68.2
unnamed: D15.4 (BA), R69.2
unnamed: D15.3 (GA), R70.2
unnamed: D15.1 (RA), R71.2
unnamed: D16.2 (BA), R72.2
unnamed: D16.3 (GA), R73.2
unnamed: D16.1 (RA), R74.2
unnamed: D17.2 (IO2), J6.2 (R), Q4.3 (D), R75.2
unnamed: D18.2 (IO2), J7.2, R81.1, R82.2
unnamed: Q2.1 (G), R17.1, R18.1
unnamed: D4.1, Q3.3 (D)
unnamed: Q3.1 (G), R23.2, R24.2
unnamed: Q4.1 (G), R76.2, R77.1
unnamed: R47.1, VR1.2
unnamed: R52.1, VR2.2
unnamed: R57.1, VR3.2
unnamed: R60.1, VR4.2
unnamed: R63.1, VR5.2
unnamed: R64.1, VR6.2
unnamed: R65.1, VR7.2
unnamed: R45.2, SW2.1 (A)
unnamed: C4.2, L1.1, U2.6 (VOUT)
unnamed: L2.1, U3.7 (SW)
unnamed: R7.1, U5.5 (PROG)
unnamed: C18.2, R13.1, U6.5 (BAT)
unnamed: R9.2, U6.2 (COUT)
unnamed: R11.2, U6.3 (DOUT)
unnamed: R12.1, U6.6 (V-)
unnamed: L4.2, U7.3 (L)
unnamed: R20.2, U7.8 (PS)
unnamed: R21.2, R23.1, U8.5 (ST)
unnamed: C26.1, L5.1, R21.1, R22.1, U8.6 (VOUT)
unnamed: R26.1, U9.14 (VOUTA)
unnamed: R27.1, U9.10 (VOUTB)
unnamed: R31.1, U11.5 (CH4)
unnamed: R32.1, U11.6 (CH5)
unnamed: R33.1, U11.7 (CH6)
unnamed: R34.1, U11.8 (CH7)
unnamed: R38.2, U12.15 (IO3)
unnamed: R39.2, U12.17 (IO9)
unnamed: R40.2, U12.18 (IO10)
unnamed: R41.2, U12.19 (IO11)
unnamed: R42.2, U12.20 (IO12)
unnamed: R43.1, U12.21 (IO13)
unnamed: R36.2, U12.13 (IO19)
unnamed: R37.2, U12.14 (IO20)
unnamed: C54.2, R61.2, R62.1, U13.6 (OUT)
unnamed: C59.2, R66.1, R67.2, U14.3 (IN+)
unnamed: R28.2, U15.1 (OUTA), U15.2 (-INA)
unnamed: R29.1, U15.6 (-INB), U15.7 (OUTB)
Noise: C56.2, R63.2, U11.1 (CH0)
OscilloscopeStimulus: C63.2, D19.3, R82.1, U11.4 (CH3)
PhotoDiode: C55.2, R62.2, U10.6 (CH5)
PhotoGain: C51.2, R60.2, U10.5 (CH4)
SCK: R42.1, U9.4 (SCK), U10.13 (CLK), U11.13 (CLK)
Spike_BLED: R72.1, U12.24 (IO47)
Spike_Buzzer: C62.1, U12.11 (IO18)
Spike_GLED: R73.1, U12.22 (IO14)
Spike_RLED: R74.1, U12.23 (IO21)
Stim_BLED: R69.1, U12.6 (IO6)
Stim_GLED: R70.1, U12.7 (IO7)
Stim_RLED: R71.1, U12.5 (IO5)
StimulusFrequency: C58.2, R65.2, U11.3 (CH2)
StimulusStrength: C57.2, R64.2, U11.2 (CH1)
Synapse1_Spike: D7.3, R51.2, U12.31 (IO38)
Synapse2_Spike: D10.3, R56.2, U12.32 (IO39)
SynapseGain1: C45.2, R47.2, U10.1 (CH0)
SynapseGain2: C47.2, R52.2, U10.3 (CH2)
SynapseIn1: C46.1, D6.3, R50.2, U10.2 (CH1)
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
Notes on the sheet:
Spike Buttons
Board power tree, source selection, battery management, control electronics, analogue acquisition and external signal interfaces. Distributes power from USB or battery operation and routes the front-panel controls, analogue readout and output signals to the main controller.
LiPo Battery Charger
Synapse 1
This section converts the photodiode current into a measurable voltage using an analogue front-end with gain and filtering. It provides the controller with a conditioned light-response signal.
This section acquires the front-panel control associated with membrane voltage behaviour. It provides a stable analogue control value to the ADC so the firmware can adjust the neuron model accordingly.
Combines the available 5 V sources into the main +5V rail while preventing reverse current between them. Forms the primary 5 V distribution node for the rest of the board. Isolates USB power from the battery-boosted supply.
This section drives the external synaptic output connector with the buffered output signal generated by the system. It provides a protected, low-impedance interface for patching the board to external equipment or other units.
ESP32 Buttons
This section converts controller-generated digital values into analogue voltages and buffers them before they are sent to external outputs. It provides controlled low-impedance analogue drive for stimulus and related output signals.
Converts the main +5V rail into the regulated +3.3V digital supply used by the controller and digital peripherals. Provides the main low-voltage logic rail for the board.
Charges the single-cell LiPo battery from USB power using a dedicated charger IC. Sets the charge current, stabilises the charger supply. Generates the battery charge node used by the protected battery path.
This section is the main digital controller of the board. It handles: USB communication Peripheral control Signal generation Data acquisition System coordination.
This section conditions the first synapse input from the external connector before it is measured or interpreted by the controller. It includes the protection and biasing needed for robust front-panel patch use.
This section digitises the analogue control voltages and sensor signals used by the system. It provides the controller with measured values from the front-panel potentiometers and analogue inputs.
Synapse 2
LiPo Battery Boost Converter
Analog to Digital Converters
Voltage Membrane
LiPo Cell Protection
This section routes selected internal signals to the external oscilloscope connection for monitoring and demonstration. It provides a convenient way to observe the generated waveforms and system activity on external instruments.
3.3 V Digital Rail Generation
Noise
Protects external connectors and user-accessible signal lines against ESD events and transient over-voltage. Reduces risk of damage or latch-up when cables are plugged, unplugged or mispatched.
Steps the protected battery voltage up to a regulated 5 V rail for stand-alone operation. Also includes the control network that allows the boost path to be enabled or inhibited depending on system power conditions.
Stimulus
This section acquires the front-panel noise control used to vary the amount of injected or simulated noise in the system. It provides an adjustable analogue parameter for the controller.
Digital to Analog Converter
This section acquires the user controls associated with stimulus amplitude and timing and generates the corresponding stimulus-related signal path. It supports both front-panel parameter control and external stimulus output.
Brings USB power and USB data onto the board. Provides the Type-C sink configuration, over-current protection and surge/ESD protection before VBUS and the USB data lines are passed into the rest of the system.
5V Lines
Photo-Receptor
ESP32-S3 WROOM1 N4
Synaptic output
Spiky Oscilloscope Interface
Protects the LiPo cell against over-charge, over-discharge and excessive current using a protection controller and back-to-back MOSFETs. Isolates the cell when unsafe operating conditions are detected.
Power, control and signal interface
USB-C entry
This section conditions the second synapse input from the external connector before it is measured or interpreted by the controller. It mirrors the first synapse path to provide a second protected and measurable input channel.

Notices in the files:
Hardware/README.md:
12. License:
Spikeling hardware is released under the **CERN Open Hardware Licence – Strongly Reciprocal v2.0 (CERN-OHL-S-2.0)**.
See:
- [`../LICENSES`](../LICENSES)
- [`../LICENSE.txt`](../LICENSE.txt)
Software and firmware are released separately under **GPL-3.0-or-later**.
If you reuse or modify the hardware, keep the appropriate license notices and attribution.
README.md:
Spikeling is released under **open-source / open-hardware** licenses:
- **Software & firmware:** **GNU General Public License v3.0** (GPL-3.0)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
